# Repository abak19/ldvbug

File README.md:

LDVBug
======

The LDVBug is a mobile Robot. It was a Bachelor-Thesis at [LDV](http://www.ldv.ei.tum.de).
## Dokumentation
[Visit Project-Doku](http://www.alexander-blum.com/studium/ldvbug)

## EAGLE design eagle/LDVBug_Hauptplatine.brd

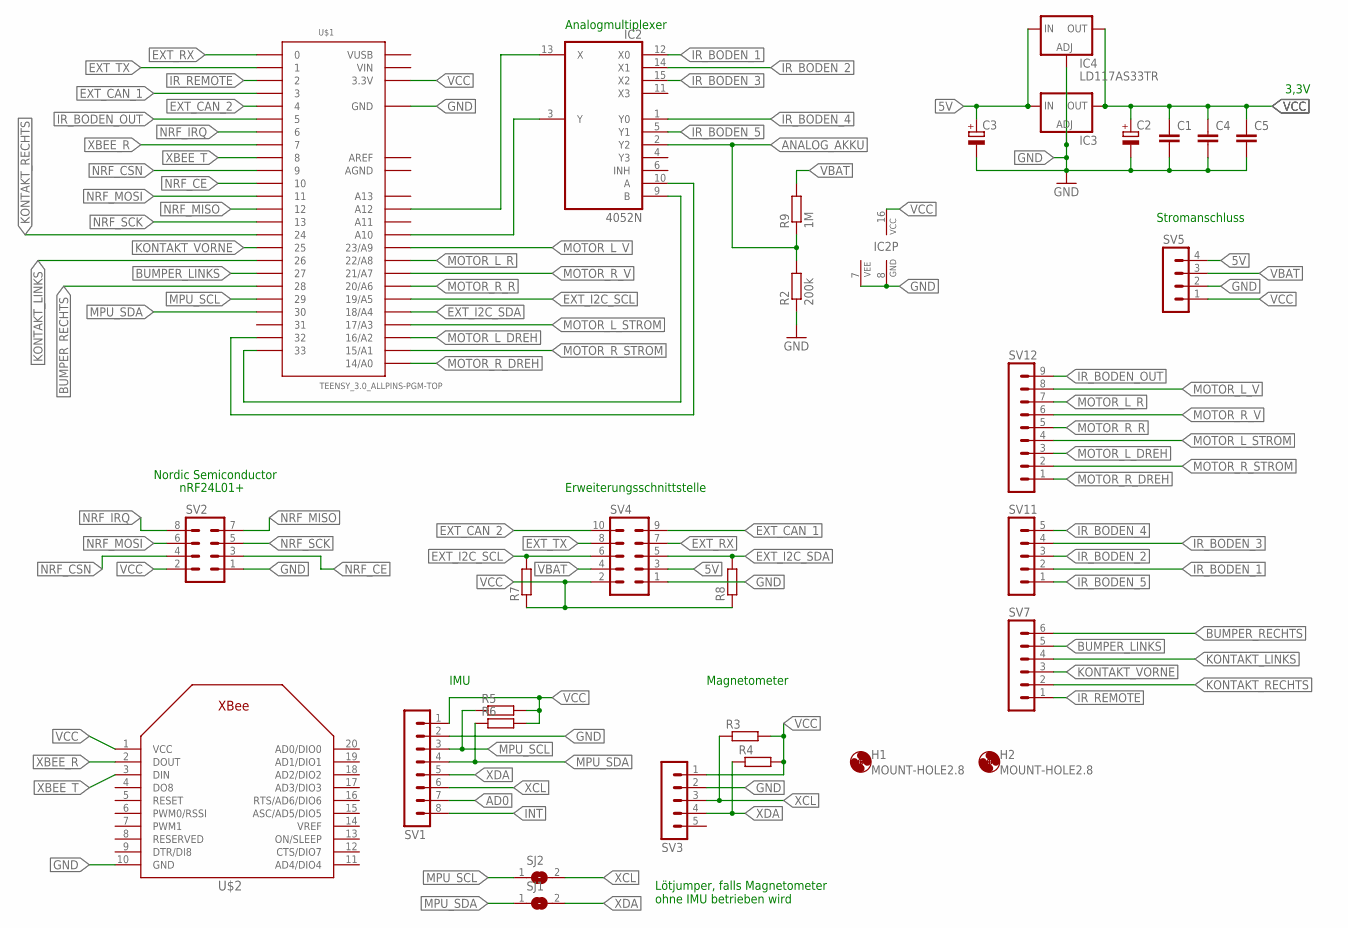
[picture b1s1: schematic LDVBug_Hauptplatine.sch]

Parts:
C1, C4, C5: C-EU025-025X050; C025-025X050
C2, C3: CPOL-EUE2.5-7; E2,5-7
H1, H2: MOUNT-HOLE2.8; 2,8
IC2: 4052N; DIL16
IC3: LM317TS; 317TS
IC4: LD117AS33TR; SOT223
R2: 200k; 0207/10
R3, R4, R5, R6, R7, R8: R-EU_R0805; R0805
R9: 1M; 0207/15
SJ1, SJ2: SJ
SV1: MA08-1
SV2: MA04-2
SV3, SV11: MA05-1
SV4: MA05-2
SV5: MA04-1
SV7: MA06-1
SV12: MA09-1
U$1: TEENSY_3.0_ALLPINS-PGM-TOP; TEENSY_3.0_ALLPINS-PGM
U$2: XBEE

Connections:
5V: C3.+, IC3.3 (IN), IC4.3 (IN), SV4.3, SV5.4
AD0: SV1.7
AGND: U$1.AGND
ANALOG_AKKU: IC2.2 (Y2), R2.2, R9.1
AREF: U$1.AREF
BUMPER_LINKS: SV7.5, U$1.27
BUMPER_RECHTS: SV7.6, U$1.28
EXT_CAN_1: SV4.9, U$1.3
EXT_CAN_2: SV4.10, U$1.4
EXT_I2C_SCL: R7.2, SV4.6, U$1.19/A5
EXT_I2C_SDA: R8.2, SV4.5, U$1.18/A4
EXT_RX: SV4.7, U$1.0
EXT_TX: SV4.8, U$1.1
GND: C1.2, C2.-, C3.-, C4.2, C5.2, IC2.7 (VEE), IC2.8 (GND), IC3.1 (ADJ), IC4.1 (ADJ), R2.1, SV1.2, SV2.1, SV3.2, SV4.1, SV5.2, U$1.GND, U$1.GND2 (GND), U$2.10 (GND)
INT: SV1.8
IR_BODEN_1: IC2.12 (X0), SV11.2
IR_BODEN_2: IC2.14 (X1), SV11.3
IR_BODEN_3: IC2.15 (X2), SV11.4
IR_BODEN_4: IC2.1 (Y0), SV11.5
IR_BODEN_5: IC2.5 (Y1), SV11.1
IR_BODEN_OUT: SV12.9, U$1.5
IR_REMOTE: SV7.1, U$1.2
KONTAKT_LINKS: SV7.4, U$1.26
KONTAKT_RECHTS: SV7.2, U$1.24
KONTAKT_VORNE: SV7.3, U$1.25
MOTOR_L_DREH: SV12.3, U$1.16/A2
MOTOR_L_R: SV12.7, U$1.22/A8
MOTOR_L_STROM: SV12.4, U$1.17/A3
MOTOR_L_V: SV12.8, U$1.23/A9
MOTOR_R_DREH: SV12.1, U$1.14/A0
MOTOR_R_R: SV12.5, U$1.20/A6
MOTOR_R_STROM: SV12.2, U$1.15/A1
MOTOR_R_V: SV12.6, U$1.21/A7
MPU_SCL: R5.1, SJ2.1, SV1.3, U$1.29
MPU_SDA: R6.1, SJ1.1, SV1.4, U$1.30
unnamed: IC2.13 (X), U$1.A12
unnamed: IC2.3 (Y), U$1.A10
unnamed: IC2.9 (B), U$1.33
unnamed: IC2.10 (A), U$1.32
NRF_CE: SV2.3, U$1.10
NRF_CSN: SV2.4, U$1.9
NRF_IRQ: SV2.8, U$1.6
NRF_MISO: SV2.7, U$1.12
NRF_MOSI: SV2.6, U$1.11
NRF_SCK: SV2.5, U$1.13
VBAT: R9.2, SV4.4, SV5.3
VCC: C1.1, C2.+, C4.1, C5.1, IC2.16 (VCC), IC3.2 (OUT), IC4.4 (OUT), R3.2, R4.2, R5.2, R6.2, R7.1, R8.1, SV1.1, SV2.2, SV3.1, SV4.2, SV5.1, U$1.3.3V, U$1.3.3V2 (3.3V), U$2.1 (VCC)
VIN: U$1.VIN
VUSB: U$1.VUSB
XBEE_R: U$1.7, U$2.2 (DOUT)
XBEE_T: U$1.8, U$2.3 (DIN)
XCL: R3.1, SJ2.2, SV1.6, SV3.3
XDA: R4.1, SJ1.2, SV1.5, SV3.4

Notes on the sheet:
3,3V
Nordic Semiconductor
nRF24L01+
Erweiterungsschnittstelle
IMU
Magnetometer
Analogmultiplexer
Stromanschluss
Lötjumper, falls Magnetometer ohne IMU betrieben wird

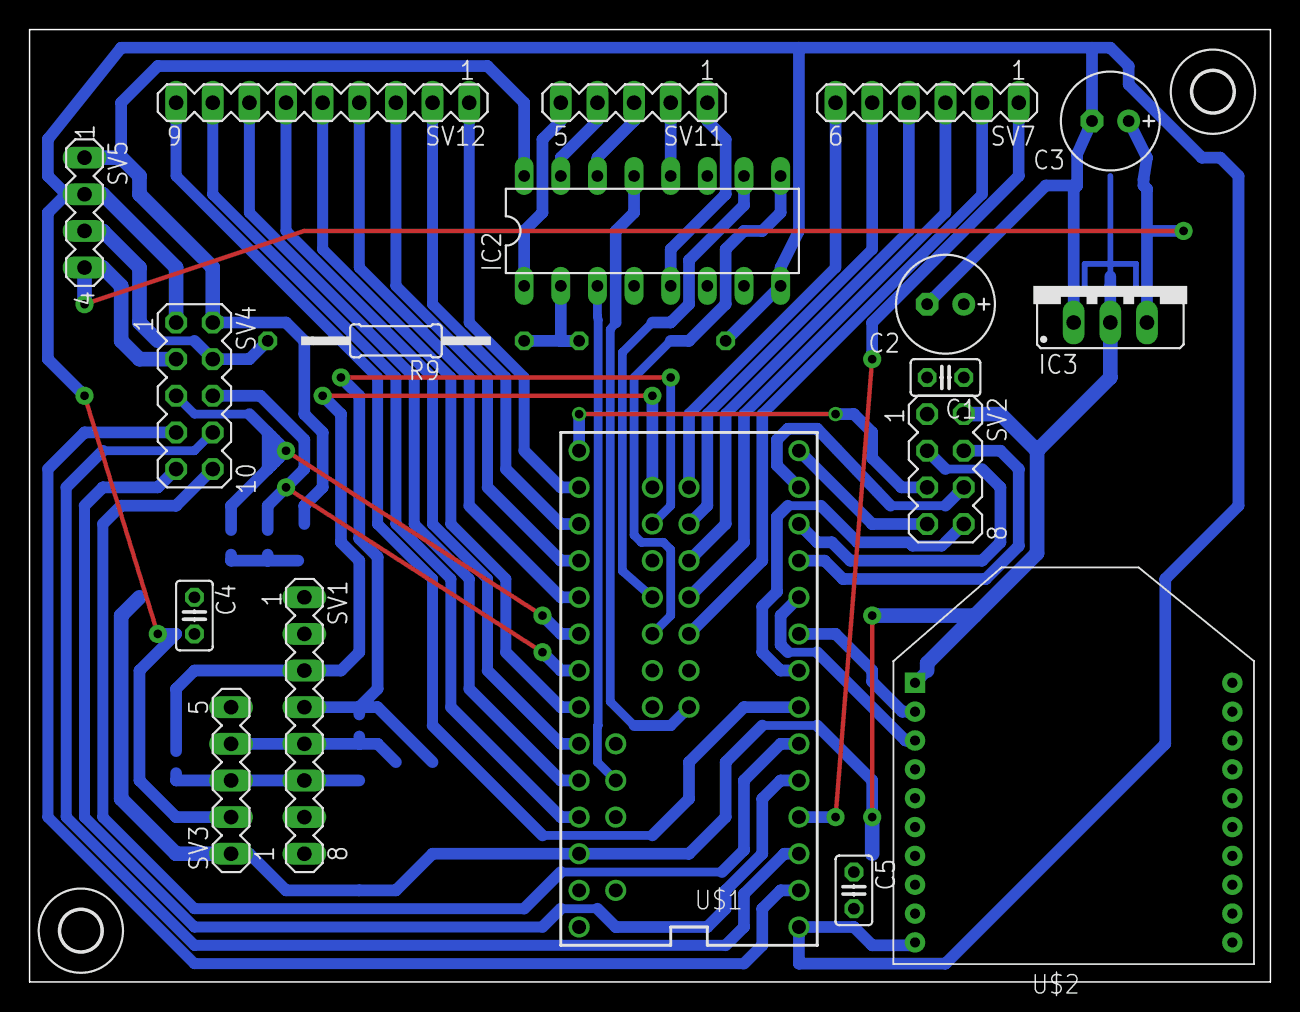
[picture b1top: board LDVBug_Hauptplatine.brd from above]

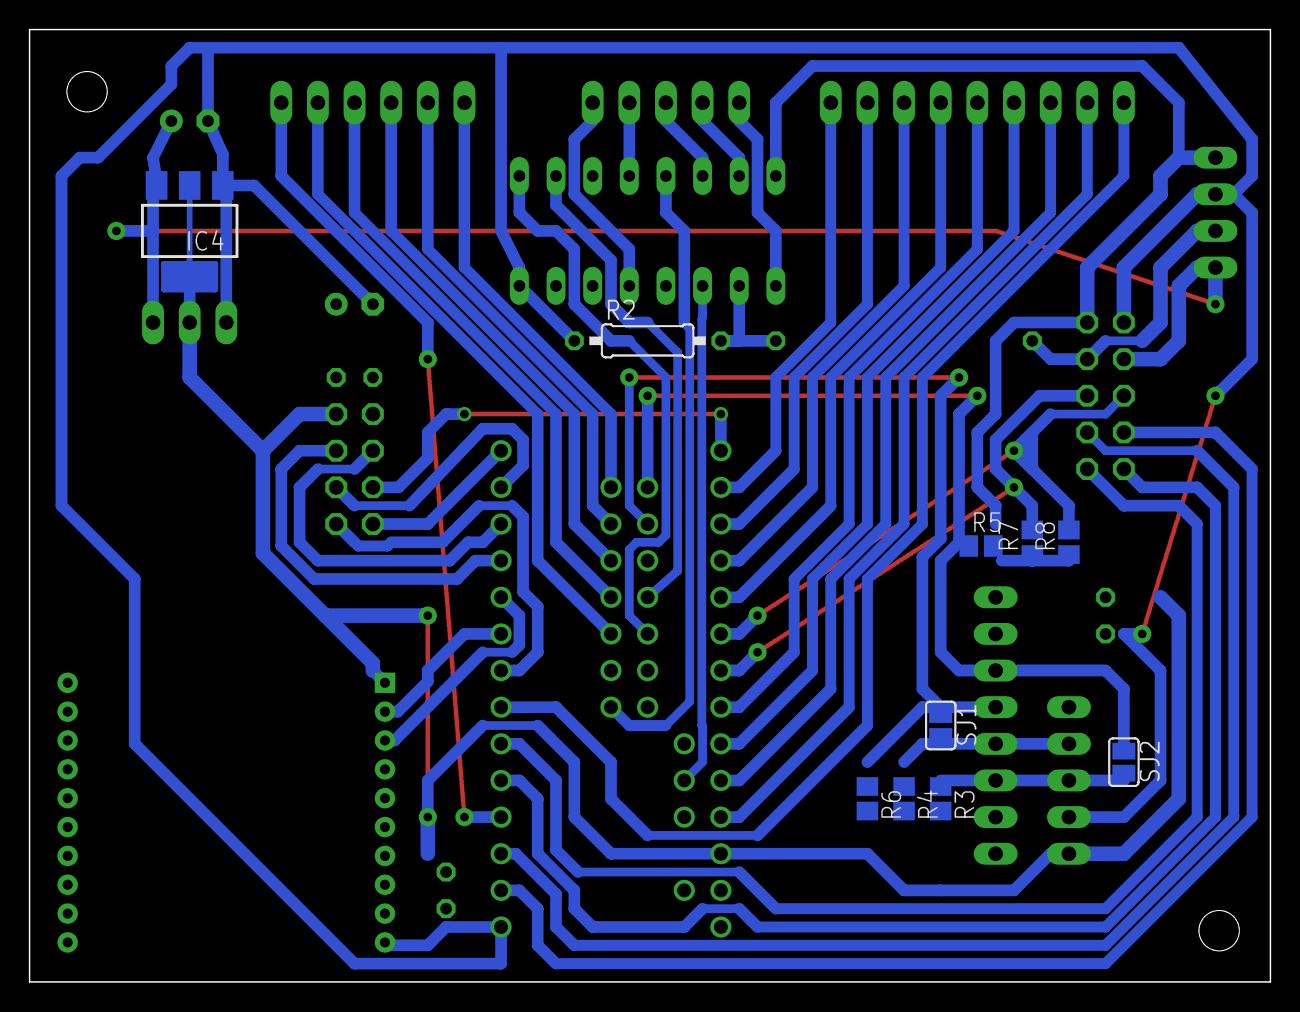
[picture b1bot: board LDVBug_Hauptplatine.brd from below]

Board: 2 copper layers, 86.0 x 66.0 mm, 30 parts (10 on the bottom side), 47 nets.

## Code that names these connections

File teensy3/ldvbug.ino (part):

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


#define MOTOR_R_DREH	14
#define MOTOR_R_STROM	15
#define MOTOR_L_DREH	16
#define MOTOR_L_STROM	17


#define KONTAKT_RECHTS	24
#define KONTAKT_VORNE	25
#define KONTAKT_LINKS	26
#define BUMPER_LINKS	27
#define BUMPER_RECHTS	28

#define MUX_A 32
#define MUX_B 33
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  pinMode(MOTORRV, OUTPUT);
  pinMode(MOTORLR, OUTPUT);
  pinMode(MOTORLV, OUTPUT);
  pinMode(MOTOR_L_DREH, INPUT);
  pinMode(MOTOR_R_DREH, INPUT);
  pinMode(MOTOR_L_STROM, INPUT);
  pinMode(MOTOR_R_STROM, INPUT);
  analogWriteFrequency(MOTORRV, 150);
  
  //attachInterrupt(14, ISR_MR, CHANGE);
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void contacts(){
  stopMovement();
  byte t=0;
  if (digitalRead(KONTAKT_LINKS)) t+=1;
  if (digitalRead(KONTAKT_VORNE)) t+=2;
  if (digitalRead(KONTAKT_RECHTS)) t+=4;
  if (digitalRead(BUMPER_LINKS)) t+=8;
  if (digitalRead(BUMPER_RECHTS)) t+=16;
  Serial.write(byte(0xEA));
  Serial.write((byte)0x04);
  Serial.write((byte)0x69);
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  motorSetup ();
  //Serial.begin(9600);
  Serial.begin(38400);
  pinMode(KONTAKT_RECHTS, INPUT);
  pinMode(KONTAKT_VORNE, INPUT);
  pinMode(KONTAKT_LINKS, INPUT);
  pinMode(BUMPER_LINKS, INPUT);
  pinMode(BUMPER_RECHTS, INPUT);
  
  //pinModeOD(IR_PWM, OUTPUT_OPEN_DRAIN);
  
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                        break;
                        case 3:{//contactswitches 104
                          byte t=0;
                          if (digitalRead(KONTAKT_LINKS)) t+=1;
                          if (digitalRead(KONTAKT_VORNE)) t+=2;
                          if (digitalRead(KONTAKT_RECHTS)) t+=4;
                          if (!digitalRead(BUMPER_LINKS)) t+=8;
                          if (!digitalRead(BUMPER_RECHTS)) t+=16;
                          Serial.write(byte(0xEA));
                          Serial.write((byte)0x04);
                          Serial.write((byte)0x69);
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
